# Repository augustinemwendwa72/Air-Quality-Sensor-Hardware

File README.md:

# sensors.AFRICA GSM AQ Kits Hardware

## Tools used

* Autodesk Eagle

* Fusion360

## sensors.AFRICA Stack

1. Firmware - https://github.com/CodeForAfrica/sensors.AFRICA-AQ-sensors-software
2. API - https://github.com/CodeForAfricaLabs/sensors.AFRICA-AQ-api
3. Map - https://github.com/CodeForAfrica/sensors.AFRICA-AQ-map-v2

## Documentation

The Documentation is under development.

## License

GNU General Public License v3.0

sensors.AFRICA is a citizen-science focused project by Code for Africa that seeks to address data gaps by providing low cost sensors, which people can use to measure and monitor the quality of the air, water, and environment in their communities. This web app seeks to be the public portal through which most users would discover and explore the data and intiative.

Copyright (C) 2021 Code for Africa

This program is free software: you can redistribute it and/or modify
it under the terms of the GNU General Public License as published by
the Free Software Foundation, either version 3 of the License, or
(at your option) any later version.

This program is distributed in the hope that it will be useful,
but WITHOUT ANY WARRANTY; without even the implied warranty of
MERCHANTABILITY or FITNESS FOR A PARTICULAR PURPOSE. See the
GNU General Public License for more details.

You should have received a copy of the GNU General Public License
along with this program. If not, see <https://www.gnu.org/licenses/>

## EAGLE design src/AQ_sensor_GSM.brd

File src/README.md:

# sensors.AFRICA / GSM AQ sensors hardware

This folder contains the Eagle design files for the sensors.AFRICA GSM boards.

### Folders

* **AQ_sensor** The Printed Circuit Board of the AQ kit

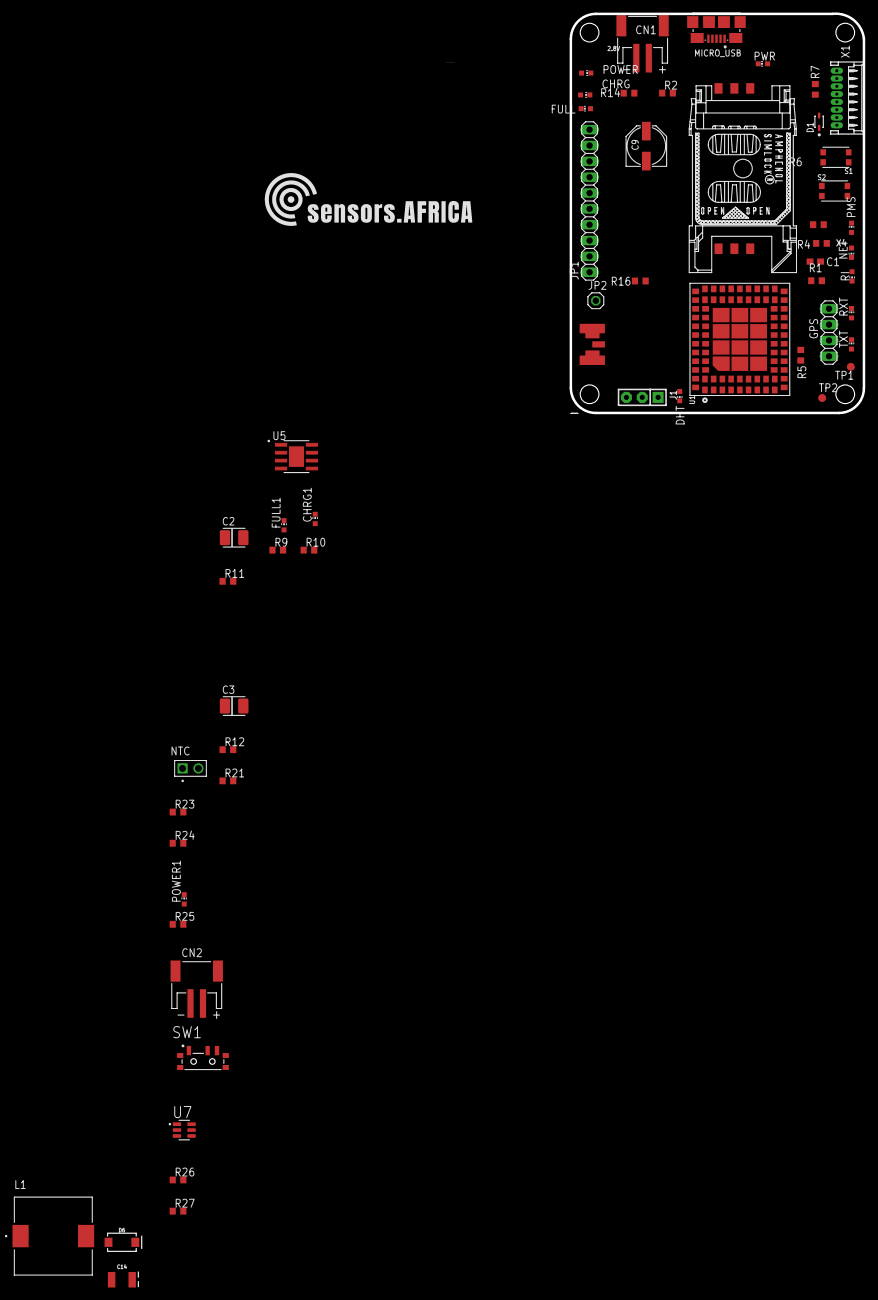
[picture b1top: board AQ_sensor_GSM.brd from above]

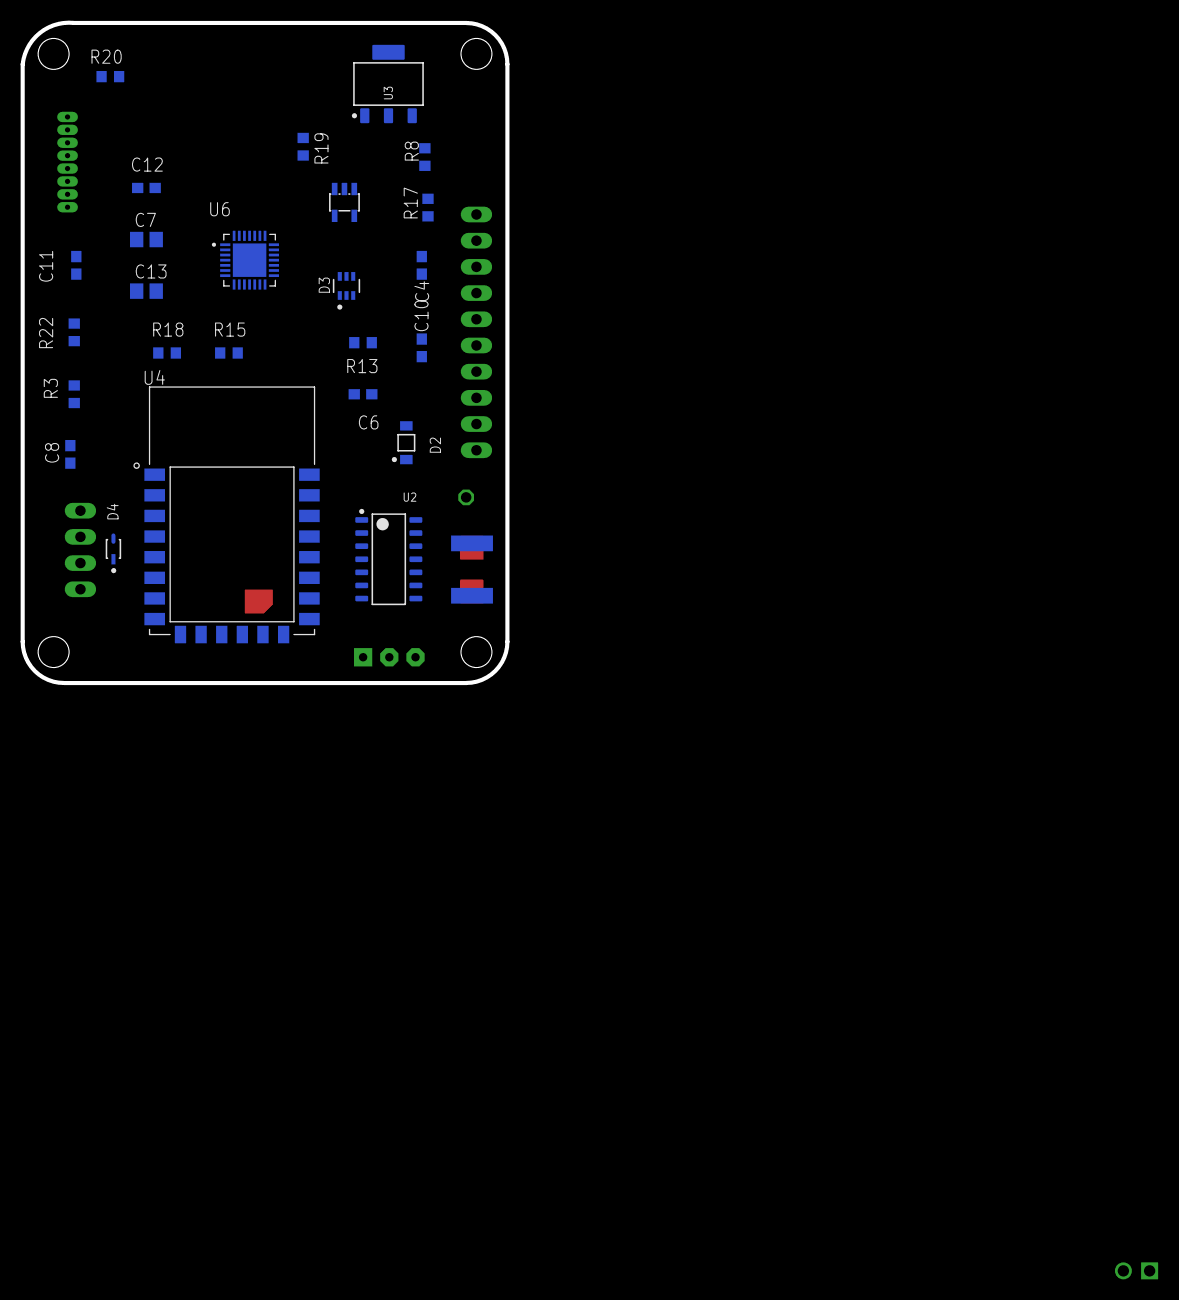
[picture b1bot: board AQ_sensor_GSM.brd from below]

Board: 2 copper layers, 47.0 x 64.0 mm, 83 parts (25 on the bottom side), 70 nets, no tracks yet.

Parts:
C1, C4, C6, C8, C12: 10uF; C0603
C2, C3: TAJB106K016RNJ; CAP_TANT_B
C7, C13: 100nF; C0805
C9: 100uF; PANASONIC_D
C10: 33pF; C0603
C11: 10pF; C0603
C14: 47uF; EIA3528
CHRG, CHRG1: RED; CHIP-LED0603
CN1, CN2: JST-PH-2-SMT-RA
D1, D4: ON_SEMI_1N4148WSON_SEMI_1N4148WS_0_0; ON_SEMI_1N4148WS_0
D2: ON_SEMICONDUCTOR_MMSZ5231BT1GON_SEMICONDUCTOR_MMS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; ON_SEMICONDUCTOR_MMSZ5231BT1G_0
D3: SEMTECH_SMF05CSEMTECH_SMF05C_0_0; SEMTECH_SMF05C_0
D6: 3A/40V/500mV; SMA-DIODE
DHT: GREEN; CHIP-LED0603
FULL, FULL1: YELLOW; CHIP-LED0603
GPS: PINHD-1X4; 1X04
IC2: MCP73831/OT; SOT23-5L
J1: F-1X03-SIP-100-32; SIP-100-03-32
JP1: PINHD-1X10; 1X10
JP2: PINHD-1X1; 1X01
L1: 47UHINDUCTOR12.5X12.5
MICRO_USB: 10118192-0001LF; AMPHENOL_10118192-0001LF
NET: YELLOW; CHIP-LED0603
NTC: 61300211121
PMS: ORANGE; CHIP-LED0603
POWER, POWER1: RED; CHIP-LED0603
PWR: RED; CHIP-LED0603
R1, R4, R6, R7, R9, R10, R16, R17, R19: 470; R0603
R2: 47k; R0603
R3: 10K; R0603
R5: 4.7K; R0603
R8, R15: 47K; R0603
R11: 1.2K; R0603
R12: 3.1K; R0603
R13: 20K; R0603
R14, R25: 1K; R0603
R18, R22: 200; R0603
R20: 2K; R0603
R21: 68K; R0603
R23: 0R; R0603
R24: 0.4R; R0603
R26: 1k; R0603
R27: 7.5k; R0603
RI: ORANGE; CHIP-LED0603
RXT: CHIP-LED0603
S1, S2: KMR621NGLFS; SW_KMR621NGLFS
SW1: PCM12SMTR; SW_PCM12SMTR
TP1, TP2: TPB1,27; B1,27
TXT: CHIP-LED0603
U1: SIM800L
U2: TEXAS_INSTRUMENTS_SN74HC125TEXAS_INSTRUMENTS_SN74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; TEXAS_INSTRUMENTS_SN74HC125_0
U3: TEXAS_INSTRUMENTS_LM1117IMP-3.3-NOPBTEXAS_INSTRUM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; TEXAS_INSTRUMENTS_LM1117IMP-3.3-NOPB_0
U4: ESP8266-12E/ESP-12E; XCVR_ESP8266-12E/ESP-12E
U5: TP4056; SOP127P600X175-9N
U6: CP2102N-A02-GQFN28; QFN50P500X500X80-29N
U7: MT3608; SOT95P280X145-6N
X1: 53048-08
X2: SIMLOCK-C707_10M006_512_2; C707_10M006_512_2
X4: 50 Ohms; SMA_EDGELAUNCH_UFL

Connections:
1.8V: D3.1, TP1.TP, U1.16, X2.C1
2.8V: TP2.TP, U1.18
5V_REG: C1.1, C14.A, D6.C, R27.2, U3.3
+3V3: C8.1, J1.3, R2.2, R3.2, R5.1, R8.2, R18.2, R22.2, U3.2, U3.4, U4.8
+5V: C6.2, C7.2, CHRG.A, GPS.1, IC2.4, JP1.1, MICRO_USB.1, R1.1, R13.1, R14.2, R24.2, U2.14, U6.7, X1.8
ADC0: JP1.9, U4.2
CHRG: R9.1, U5.7
D+: MICRO_USB.3, U6.4
D-: MICRO_USB.2, U6.5
DHT_LED: R16.2, U4.17
DHT_OUT: J1.2, R5.2, U4.7
ESP_CSO: JP1.5, U4.9
ESP_MISO: JP1.7, U4.10
ESP_MOSI: JP1.6, U4.13
ESP_RST: S2.1_1, S2.1_2, U4.1
ESP_RX: U4.21, U6.26
ESP_SCLK: JP1.4, U4.14
ESP_TX: U4.22, U6.25
GND: C1.2, C2.2, C3.2, C4.2, C6.1, C7.1, C8.2, C9.-, C10.2, C11.2, C12.1, C13.1, C14.C, CN1.2, CN2.2, D1.1, D2.2, D3.2, DHT.C, FULL.C, GPS.4, IC2.2, J1.1, JP1.10, MICRO_USB.4, MICRO_USB.5, MICRO_USB.SH1, MICRO_USB.SH2, MICRO_USB.SH3, MICRO_USB.SH4, MICRO_USB.SH5, MICRO_USB.SH6, NET.C, NTC.2, PMS.C, POWER.C, POWER1.C, PWR.C, R11.2, R15.2, R20.2, R21.1, R23.1, R26.1, S1.1_1, S1.1_2, S2.2_1, S2.2_2, U1.2, U1.6, U1.8, U1.35, U1.37, U1.38, U1.39, U1.41, U1.43, U1.44, U1.45, U1.58, U1.67, U1.71, U1.72, U1.73, U1.76, U1.77, U1.78, U1.79, U1.80, U1.81, U1.82, U1.83, U1.84, U1.85, U1.86, U1.87, U1.88, U2.1, U2.4, U2.7, U2.10, U2.13, U3.1, U4.15, U5.3, U6.3, U6.29, U7.2, X1.7, X2.C5, X4.GND@1, X4.GND@2, X4.GND@3, X4.GND@4
GPS_RX: GPS.2, U4.11
GPS_TX: GPS.3, U4.12
GSM_ANT: JP2.1, U1.40, X4.P
GSM_RX: D4.2, U1.31
GSM_RX_O: D4.1, U4.5
GSM_TX: U1.32, U2.5
GSM_TX_5V: U2.6, U4.6
IO16: JP1.8, U4.4
unnamed: R2.1, U4.3
unnamed: R13.2, R15.1, U6.8
unnamed: PMS.A, R4.1
unnamed: R3.1, U6.9
unnamed: CHRG.C, R17.1
unnamed: R22.1, TXT.C
unnamed: R18.1, RXT.C
unnamed: IC2.1, R17.2, R19.2
unnamed: NET.A, R6.2
unnamed: PWR.A, R7.2
unnamed: FULL.A, R19.1
unnamed: IC2.5, R20.1
unnamed: R1.2, RI.A
unnamed: C12.2, C13.2, R8.1, U6.6
unnamed: R11.1, U5.2
unnamed: TXT.A, U6.19
unnamed: RXT.A, U6.18
unnamed: CHRG1.C, R9.2
unnamed: FULL1.C, R10.2
unnamed: POWER1.A, R25.1
unnamed: CN2.1, SW1.2
unnamed: D6.A, L1.2, U7.1
unnamed: POWER.A, R14.1
unnamed: R26.2, R27.1, U7.3
unnamed: DHT.A, R16.1
NETSTAT: U1.64, U2.2
NETSTAT_5V: R6.1, U2.3
PMS_LED: R4.2, U4.18
PMS_RX: U4.19, X1.5
PMS_TX: U4.20, X1.4
PWRKEY: D1.2, S1.2_1, S1.2_2, U1.48
PWRSTAT: U1.4, U2.9
PWRSTAT_5V: R7.1, U2.8
RI: U1.68, U2.12
RI_5V: RI.C, U2.11
SIMCLK: D3.3, U1.55, X2.C3
SIMDATA: D3.4, U1.14, X2.C7
SIMRST: D3.5, U1.15, X2.C2
STDBY: R10.1, U5.6
TEMP: NTC.1, R12.1, R21.2, R23.2, U5.1
TP_VCC: C2.1, CHRG1.A, FULL1.A, R12.2, R24.1, U5.4, U5.8
VRTC: C4.1, U1.56
V_LIPO: C3.1, C9.+, C10.1, C11.1, CN1.1, D2.1, IC2.3, L1.1, R25.2, SW1.1, U1.1, U1.42, U5.5, U7.4, U7.5

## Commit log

2021-08-24 Added Board design and schematic
2021-08-27 Optimized power planes
2021-08-27 Added copper fills
2021-09-28 Added stitching vias
2021-09-28 Added manufacturing files
2021-09-28 Added Bill of Materials
2021-09-28 Added board layout image
2021-09-28 Added board schematic image
2021-10-04 created src folder
2021-10-04 added license and documentation
2021-10-04 changed board type to GSM
2021-10-12 sorted DRC
2021-10-12 removed store file
2021-10-18 Organized schematic
2021-10-18 Added .github directory
2022-01-14 swapped DHT and PMS positions
2022-01-17 updated 3D models
2023-07-28 Feature: Change components' positions.
    1. Rotate NodeMCU 90 degrees anti-clockwise. 2. Add onboard GSM Antenna. 3. Move Simcard Holder to top Layer. 4. Change Reset button to push button. 5. Rearrange Charging Circuitry layout to minimise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
2023-07-28 Ripup
2023-08-14 Traces updated.
2023-08-14 Routing Completed, Power Trace Width updated, Node MCU Position and Orientation Updated.
2023-09-04 CH340 Added
2023-09-04 PCB Lay out Init
2023-09-04 Layout Update 2
2023-09-04 PCB Resized
2023-09-04 angle edges
2023-09-04 Curved Board edges
2023-09-04 Components Allignment
2023-09-04 Added Boost Circuitry
2023-09-04 Routed Minus Rasnet
2023-09-05 Updated Port positions As suggested by USMAN
2023-09-05 Components Placement Update
2023-09-11 Realign components on the top layer.
2023-09-14 Updated schematics with Simcard holder on the bottom Layer.
2023-09-26 Resolve schematic file error
    Schematic file not opening on resolving git merge conflict
2023-10-23 Changed Lipo charging IC to TP4056. Added Power Switch to the lipo Circuitry
2023-10-23 upgraded ME2108A to MT3608 Boost converter
2023-10-23 Added LC filter to the MT3608 boost circuit
2023-10-26 Add GPS Module (L80-M39)

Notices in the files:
parts and their libraries:
SparkFun-Capacitors: Licensing: Creative Commons ShareAlike 4.0 International - https://creativecommons.org/licenses/by-sa/4.0
